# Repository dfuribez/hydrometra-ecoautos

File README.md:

View this project on [CADLAB.io](https://cadlab.io/project/2164).

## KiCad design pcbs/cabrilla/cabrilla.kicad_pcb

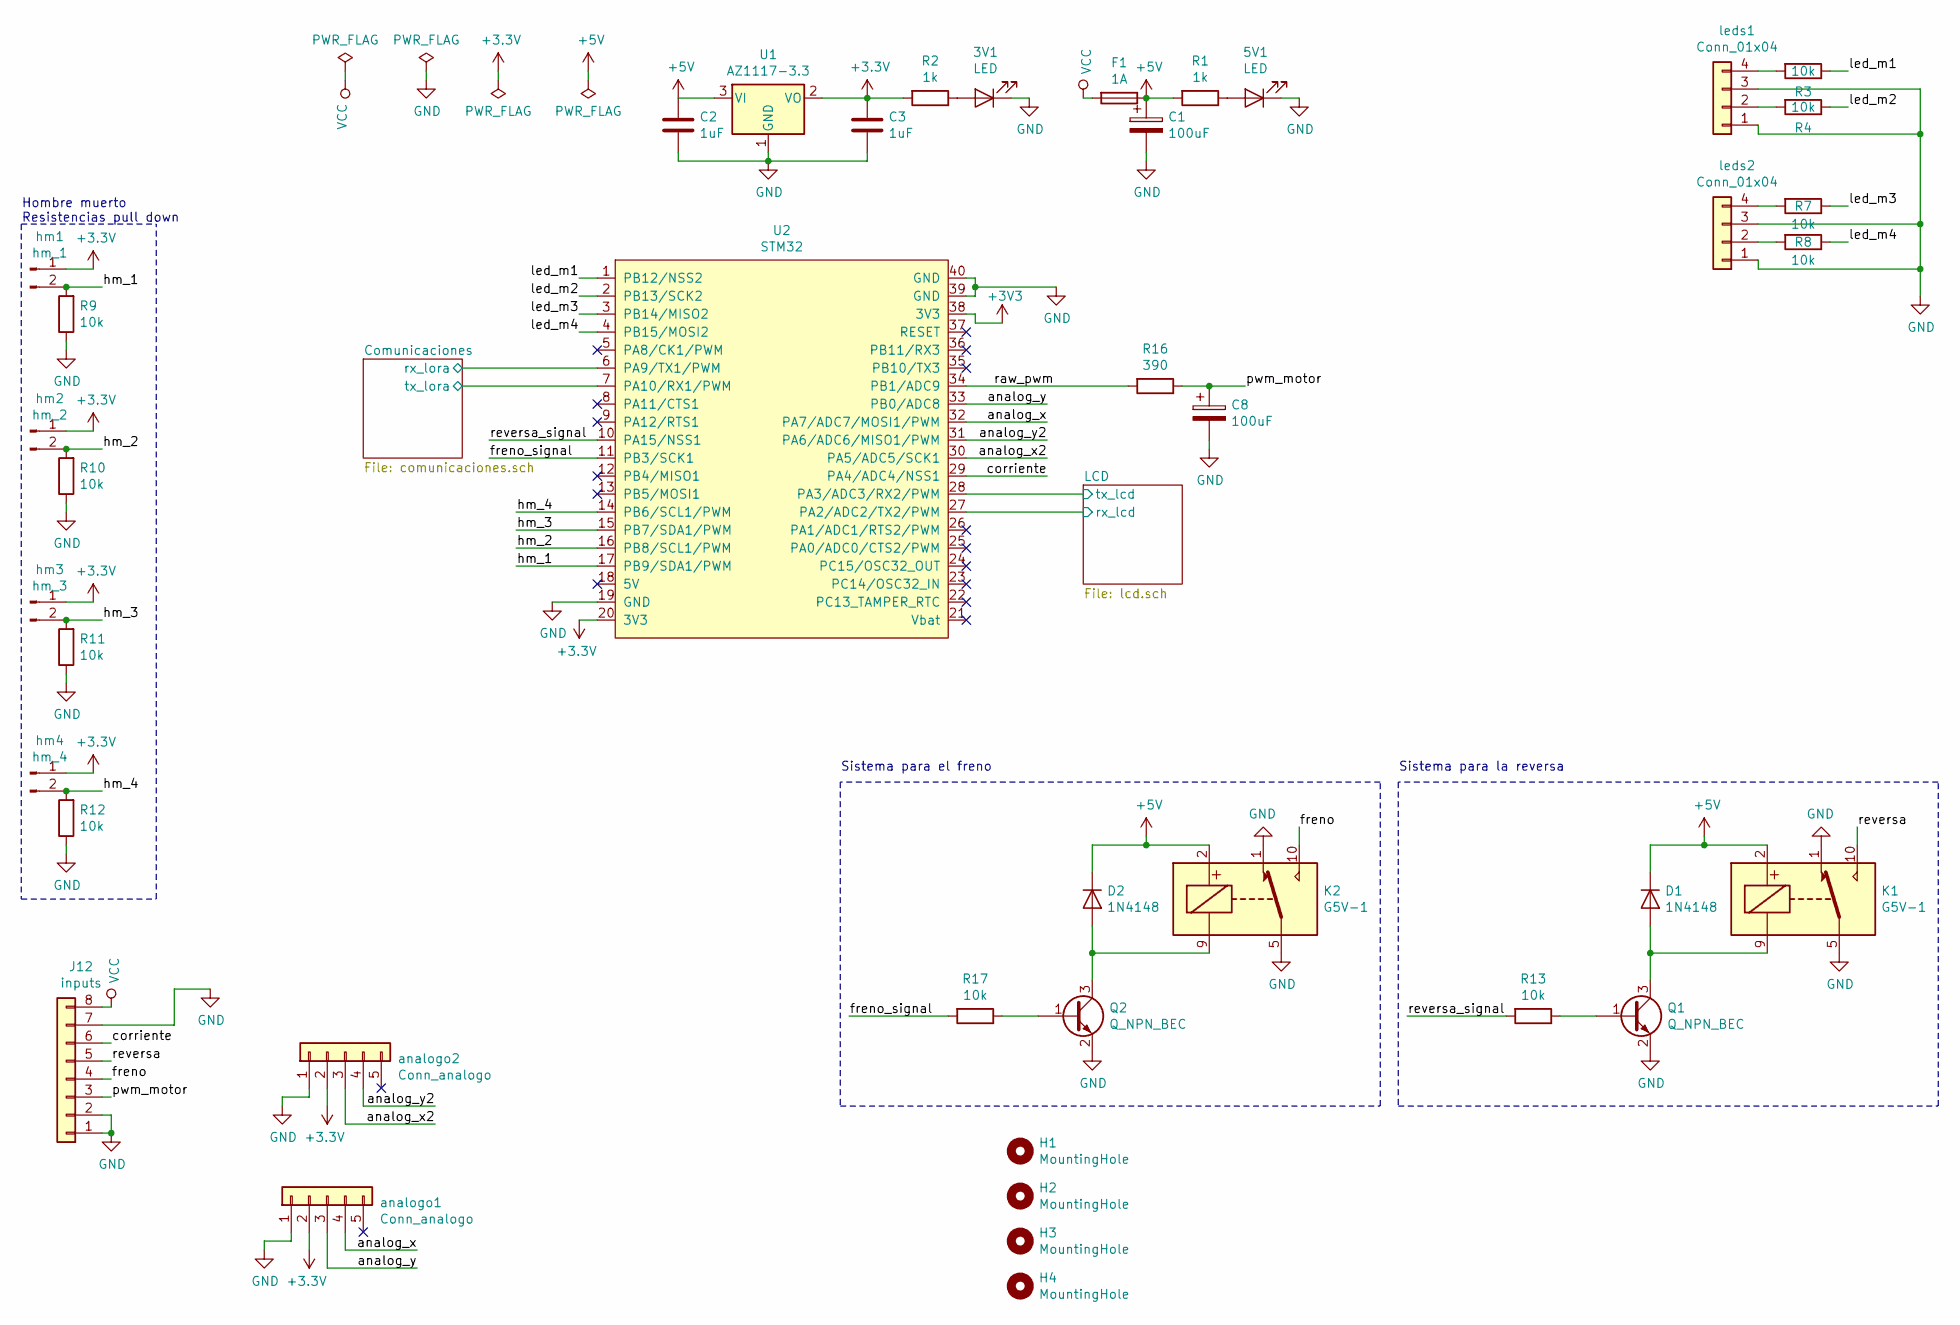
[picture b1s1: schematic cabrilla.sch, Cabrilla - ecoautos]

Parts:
3V1, 5V1: LED; LED_0805_2012Metric_Pad1.15x1.40mm_HandSolder
C1, C8: 100uF; CP_Elec_8x10
C2, C3: 1uF; C_0805_2012Metric_Pad1.15x1.40mm_HandSolder
D1, D2: 1N4148; D_SOD-323_HandSoldering
F1: 1A; Fuse_2816_7142Metric_Pad3.20x4.45mm_HandSolder
H1, H2, H3, H4: MountingHole; MountingHole_3.2mm_M3
J12: inputs; Molex_KK-254_AE-6410-08A_1x08_P2.54mm_Vertical
K1, K2: G5V-1; Relay_SPDT_Omron_G5V-1
Q1, Q2: Q_NPN_BEC; SOT-23_Handsoldering
R1, R2: 1k; R_0805_2012Metric_Pad1.15x1.40mm_HandSolder
R3, R4, R7, R8, R9, R10, R11, R12, R13, R17: 10k; R_0805_2012Metric_Pad1.15x1.40mm_HandSolder
R16: 390; R_0805_2012Metric_Pad1.15x1.40mm_HandSolder
U1: AZ1117-3.3; SOT-223
U2: STM32
analogo1, analogo2: Conn_analogo; Molex_KK-254_AE-6410-05A_1x05_P2.54mm_Vertical
hm1: hm_1; Molex_KK-254_AE-6410-02A_1x02_P2.54mm_Vertical
hm2: hm_2; Molex_KK-254_AE-6410-02A_1x02_P2.54mm_Vertical
hm3: hm_3; Molex_KK-254_AE-6410-02A_1x02_P2.54mm_Vertical
hm4: hm_4; Molex_KK-254_AE-6410-02A_1x02_P2.54mm_Vertical
leds1, leds2: Conn_01x04; Molex_KK-254_AE-6410-04A_1x04_P2.54mm_Vertical

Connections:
+5V: C1.1, C2.1, D1.1 (K), D2.1 (K), F1.1, K1.2, K2.2, R1.2, U1.3 (VI); also elsewhere on the board
/Comunicaciones/rx_lora: U2.6 (PA9/TX1/PWM); also elsewhere on the board
/Comunicaciones/tx_lora: U2.7 (PA10/RX1/PWM); also elsewhere on the board
/LCD/rx_lcd: U2.27 (PA2/ADC2/TX2/PWM); also elsewhere on the board
/LCD/tx_lcd: U2.28 (PA3/ADC3/RX2/PWM); also elsewhere on the board
/analog_x: U2.32 (PA7/ADC7/MOSI1/PWM), analogo1.4
/analog_x2: U2.30 (PA5/ADC5/SCK1), analogo2.3
/analog_y: U2.33 (PB0/ADC8), analogo1.3
/analog_y2: U2.31 (PA6/ADC6/MISO1/PWM), analogo2.4
/corriente: J12.6, U2.29 (PA4/ADC4/NSS1)
/freno: J12.4, K2.10
/freno_signal: R17.2, U2.11 (PB3/SCK1)
/hm_1: R9.2, U2.17 (PB9/SDA1/PWM), hm1.2
/hm_2: R10.2, U2.16 (PB8/SCL1/PWM), hm2.2
/hm_3: R11.2, U2.15 (PB7/SDA1/PWM), hm3.2
/hm_4: R12.2, U2.14 (PB6/SCL1/PWM), hm4.2
/led_m1: R3.1, U2.1 (PB12/NSS2)
/led_m2: R4.1, U2.2 (PB13/SCK2)
/led_m3: R7.1, U2.3 (PB14/MISO2)
/led_m4: R8.1, U2.4 (PB15/MOSI2)
/pwm_motor: C8.1, J12.3, R16.1
/raw_pwm: R16.2, U2.34 (PB1/ADC9)
/reversa: J12.5, K1.10
/reversa_signal: R13.2, U2.10 (PA15/NSS1)
GND: 3V1.1 (K), 5V1.1 (K), C1.2, C2.2, C3.2, C8.2, J12.1, J12.2, J12.7, K1.1, K1.5, K1.6, K2.1, K2.5, K2.6, Q1.2 (E), Q2.2 (E), R9.1, R10.1, R11.1, R12.1, U1.1 (GND), U2.19 (GND), U2.39 (GND), U2.40 (GND), analogo1.1, analogo2.1, leds1.1, leds1.3, leds2.1, leds2.3; also elsewhere on the board
unnamed: 3V1.2 (A), R2.1
unnamed: 5V1.2 (A), R1.1
unnamed: D1.2 (A), K1.9, Q1.3 (C)
unnamed: D2.2 (A), K2.9, Q2.3 (C)
unnamed: Q1.1 (B), R13.1
unnamed: Q2.1 (B), R17.1
unnamed: R3.2, leds1.4
unnamed: R4.2, leds1.2
unnamed: R7.2, leds2.4
unnamed: R8.2, leds2.2
VCC: F1.2, J12.8

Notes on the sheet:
Hombre muerto Resistencias pull down
Sistema para la reversa
Sistema para el freno

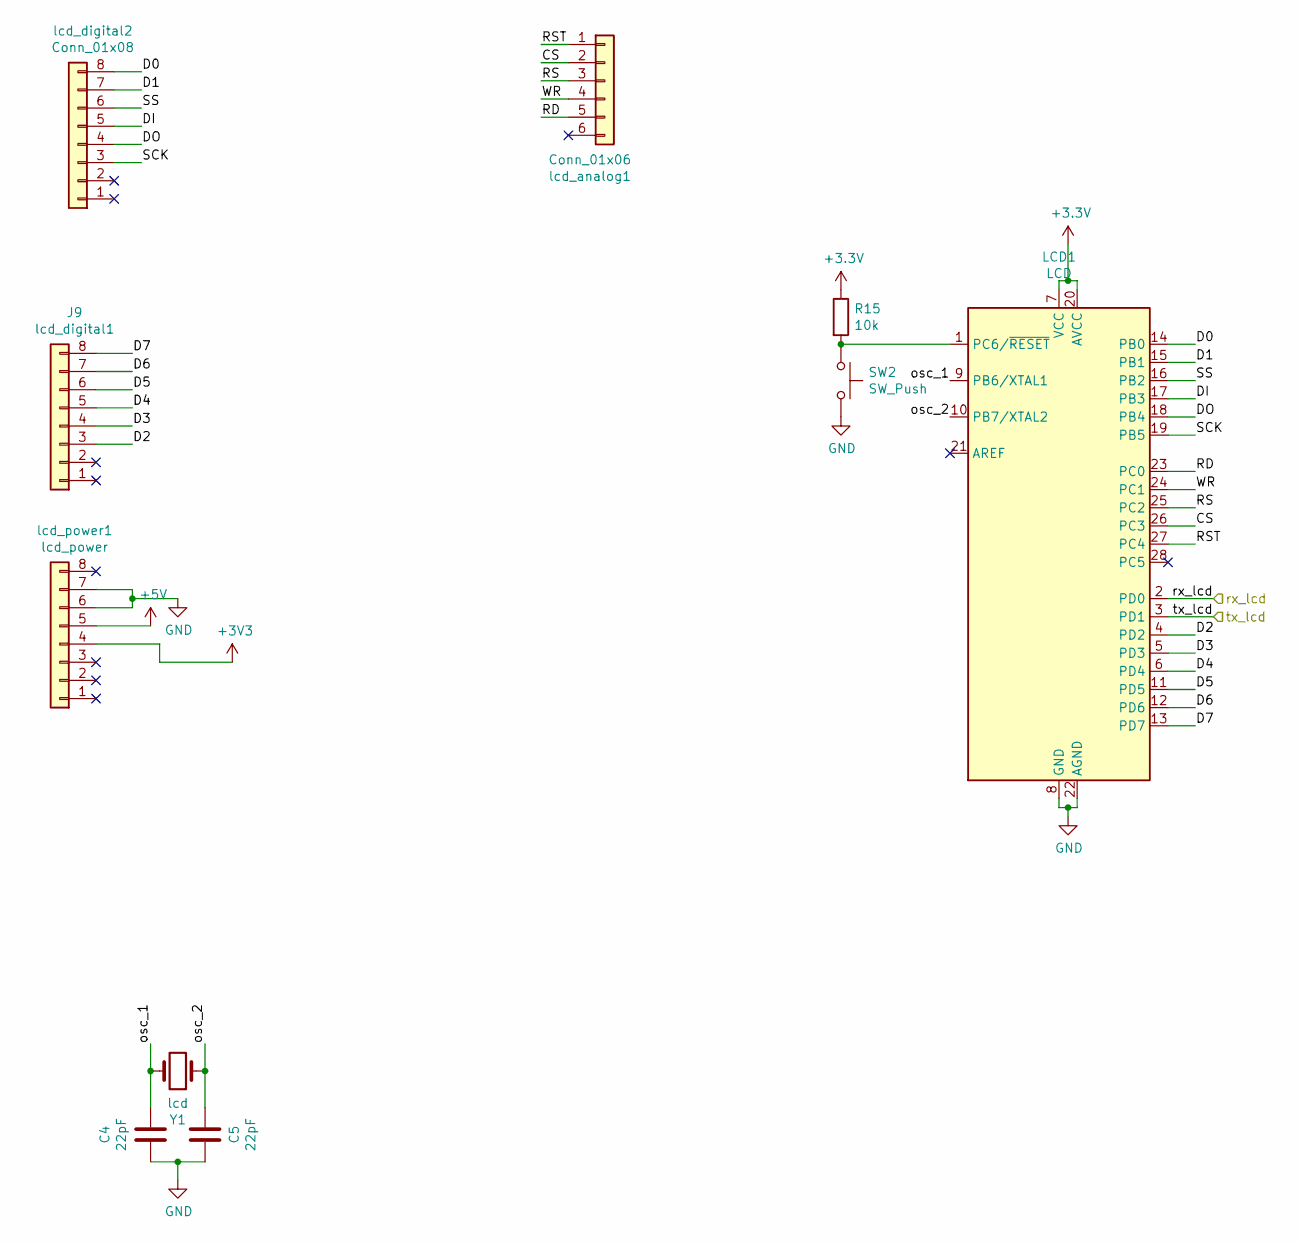
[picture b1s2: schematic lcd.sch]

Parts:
C4, C5: 22pF; C_0805_2012Metric_Pad1.15x1.40mm_HandSolder
J9: lcd_digital1; Molex_KK-254_AE-6410-08A_1x08_P2.54mm_Vertical
LCD1: LCD; DIP-28_W7.62mm_Socket
R15: 10k; R_0805_2012Metric_Pad1.15x1.40mm_HandSolder
SW2: SW_Push; SW_Push_1P1T_NO_CK_KSC6xxJ
Y1: lcd; Crystal_HC49-4H_Vertical
lcd_analog1: Conn_01x06; Molex_KK-254_AE-6410-06A_1x06_P2.54mm_Vertical
lcd_digital2: Conn_01x08; Molex_KK-254_AE-6410-08A_1x08_P2.54mm_Vertical
lcd_power1: lcd_power; Molex_KK-254_AE-6410-08A_1x08_P2.54mm_Vertical

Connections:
+5V: lcd_power1.5; also elsewhere on the board
/LCD/CS: LCD1.26 (PC3), lcd_analog1.2
/LCD/D0: LCD1.14 (PB0), lcd_digital2.8
/LCD/D1: LCD1.15 (PB1), lcd_digital2.7
/LCD/D2: J9.3, LCD1.4 (PD2)
/LCD/D3: J9.4, LCD1.5 (PD3)
/LCD/D4: J9.5, LCD1.6 (PD4)
/LCD/D5: J9.6, LCD1.11 (PD5)
/LCD/D6: J9.7, LCD1.12 (PD6)
/LCD/D7: J9.8, LCD1.13 (PD7)
/LCD/DI: LCD1.17 (PB3), lcd_digital2.5
/LCD/DO: LCD1.18 (PB4), lcd_digital2.4
/LCD/RD: LCD1.23 (PC0), lcd_analog1.5
/LCD/RS: LCD1.25 (PC2), lcd_analog1.3
/LCD/RST: LCD1.27 (PC4), lcd_analog1.1
/LCD/SCK: LCD1.19 (PB5), lcd_digital2.3
/LCD/SS: LCD1.16 (PB2), lcd_digital2.6
/LCD/WR: LCD1.24 (PC1), lcd_analog1.4
/LCD/osc_1: C4.2, LCD1.9 (PB6/XTAL1), Y1.2
/LCD/osc_2: C5.2, LCD1.10 (PB7/XTAL2), Y1.1
/LCD/rx_lcd: LCD1.2 (PD0); also elsewhere on the board
/LCD/tx_lcd: LCD1.3 (PD1); also elsewhere on the board
GND: C4.1, C5.1, LCD1.8 (GND), LCD1.22 (AGND), SW2.2, lcd_power1.6, lcd_power1.7; also elsewhere on the board
unnamed: LCD1.1 (PC6/~RESET), R15.2, SW2.1

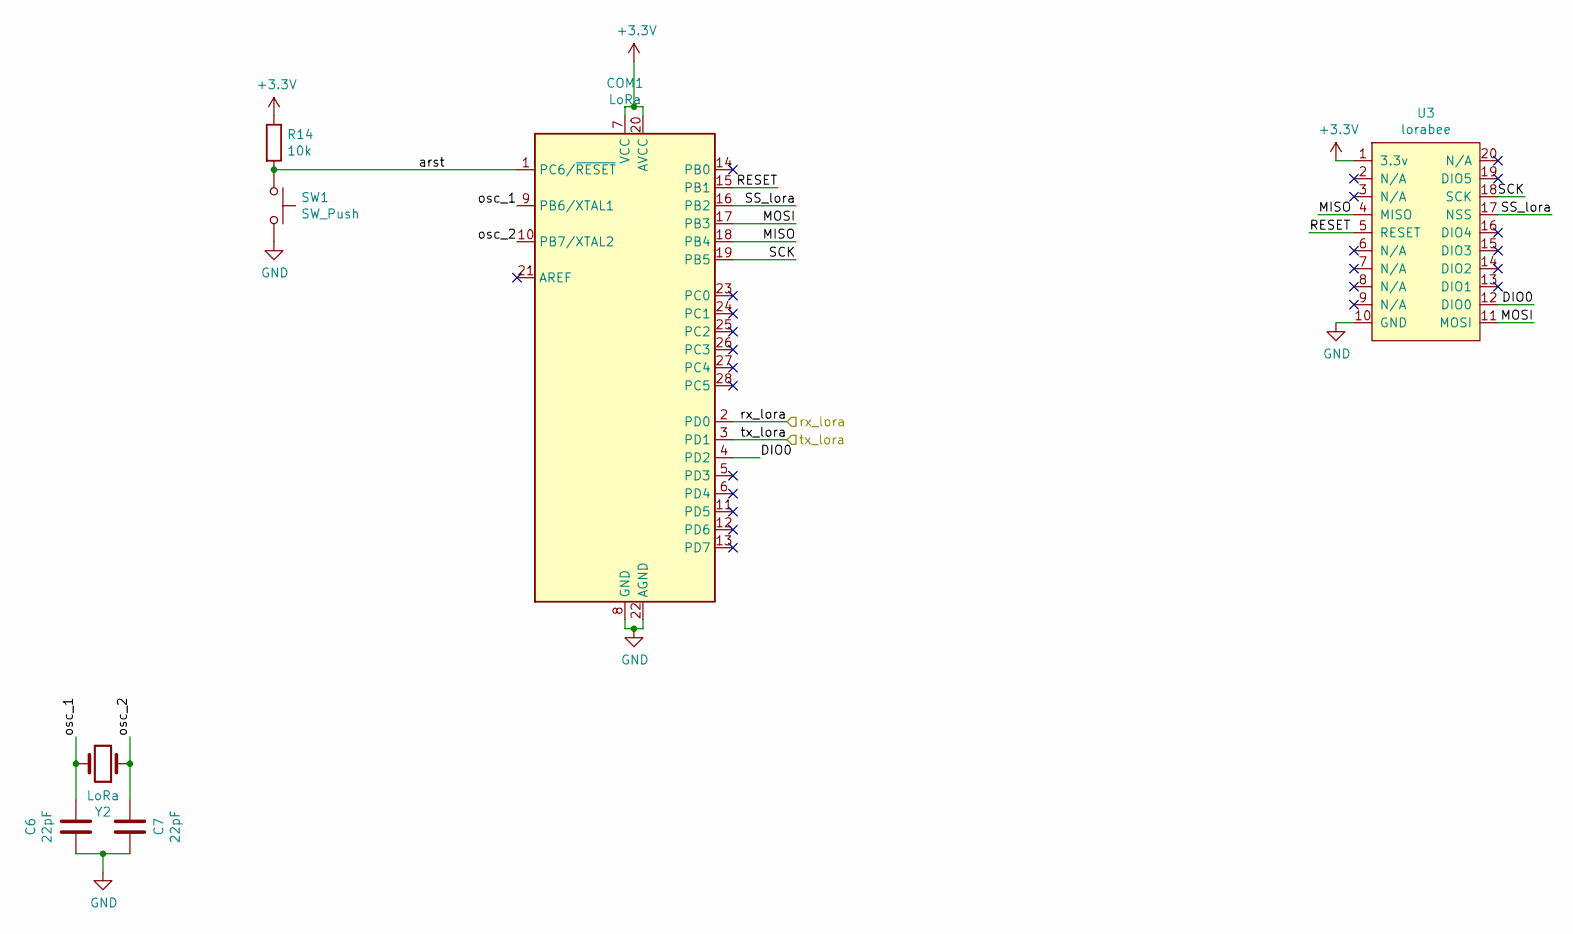
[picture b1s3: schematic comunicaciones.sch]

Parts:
C6, C7: 22pF; C_0805_2012Metric_Pad1.15x1.40mm_HandSolder
COM1: LoRa; DIP-28_W7.62mm_Socket
R14: 10k; R_0805_2012Metric_Pad1.15x1.40mm_HandSolder
SW1: SW_Push; SW_Push_1P1T_NO_CK_KSC6xxJ
U3: lorabee
Y2: LoRa; Crystal_HC49-4H_Vertical

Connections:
/Comunicaciones/DIO0: COM1.4 (PD2), U3.12 (DIO0)
/Comunicaciones/MISO: COM1.18 (PB4), U3.4 (MISO)
/Comunicaciones/MOSI: COM1.17 (PB3), U3.11 (MOSI)
/Comunicaciones/RESET: COM1.15 (PB1), U3.5 (RESET)
/Comunicaciones/SCK: COM1.19 (PB5), U3.18 (SCK)
/Comunicaciones/SS_lora: COM1.16 (PB2), U3.17 (NSS)
/Comunicaciones/arst: COM1.1 (PC6/~RESET), R14.2, SW1.1
/Comunicaciones/osc_1: C6.2, COM1.9 (PB6/XTAL1), Y2.2
/Comunicaciones/osc_2: C7.2, COM1.10 (PB7/XTAL2), Y2.1
/Comunicaciones/rx_lora: COM1.2 (PD0); also elsewhere on the board
/Comunicaciones/tx_lora: COM1.3 (PD1); also elsewhere on the board
GND: C6.1, C7.1, COM1.8 (GND), COM1.22 (AGND), SW1.2, U3.10 (GND); also elsewhere on the board

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
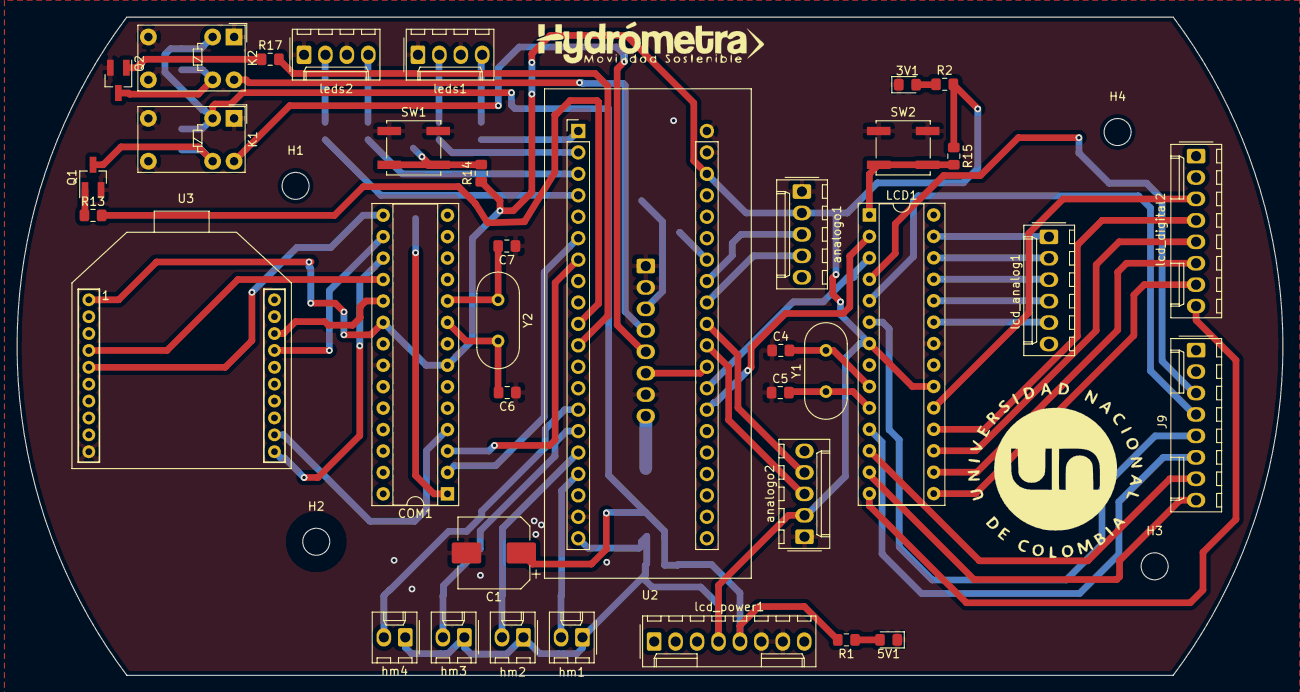
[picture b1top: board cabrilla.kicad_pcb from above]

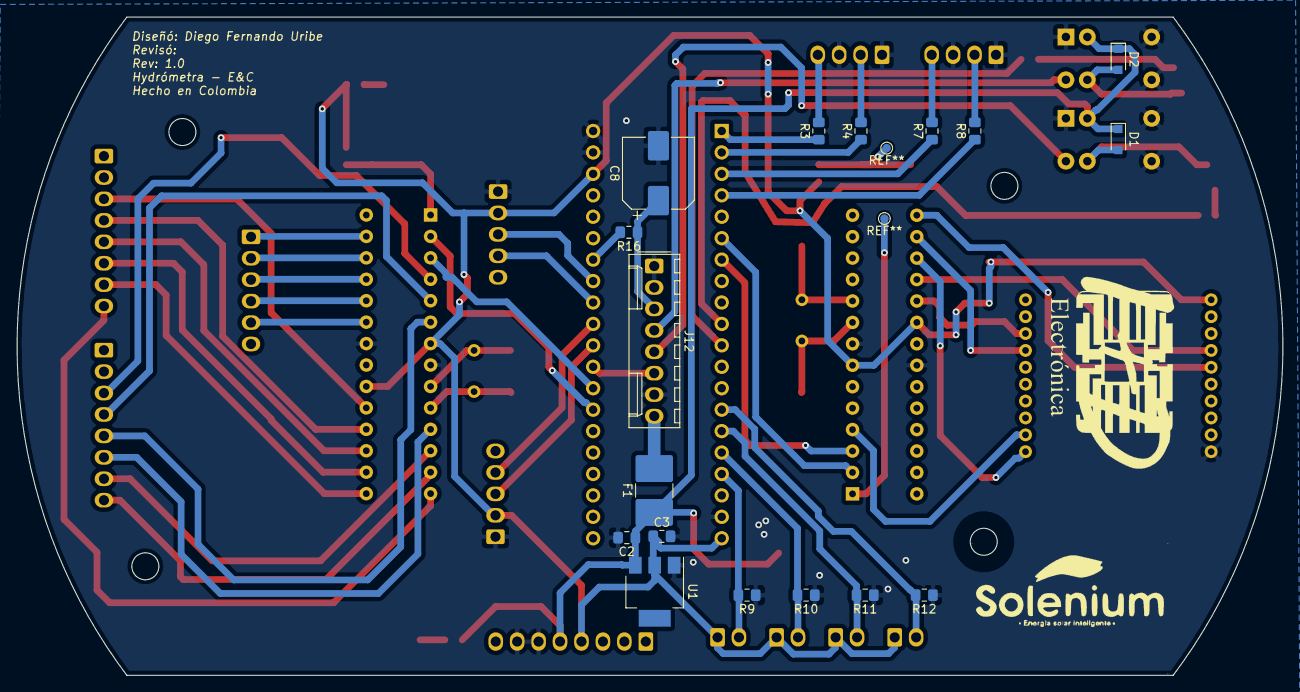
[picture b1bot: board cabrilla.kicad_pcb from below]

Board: 2 copper layers, 150.0 x 78.0 mm, 58 parts (17 on the bottom side), 66 nets.

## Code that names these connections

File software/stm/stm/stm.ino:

// Variables

// Análogo #1
uint16_t analog_x1 = 0;
uint16_t analog_y1 = 0;

// Análogo #2
uint16_t analog_x2 = 0;
uint16_t analog_y2 = 0;

uint8_t hm_counter = 0;


// Banderas interrupciones
bool flag_hm = 0;
bool flag_timer = 0;



// Pines

// Leds
#define LED_1_PIN   PB12
#define LED_2_PIN   PB13
#define LED_3_PIN   PB14
#define LED_4_PIN   PB15

#define REVERSA_PIN PA12
#define FRENO_PIN   PB3

// Hombre muerto
#define HM_1_PIN    PB6
#define HM_2_PIN    PB7
#define HM_3_PIN    PB8
#define HM_4_PIN    PB9

#define RAW_PWM_PIN     PB1

#define ANALOG_Y1_PIN   PB0
#define ANALOG_X1_PIN   PA7
#define ANALOG_Y2_PIN   PA6
#define ANALOG_X2_PIN   PA5

#define CORRIENTE_PIN   PA4


HardwareTimer timer(1);

// Definiciones
void isr_hm(void);  // Interrupción boton hombre muerto
void isr_timer(void);  // Interrupción timer hombre muerto

uint16_t read_analog(uint8_t pin);  // Lectura análoga
void generate_pwm(uint16_t valor); // Genera el pwm


void setup() {
  Serial.begin(115200);  // comunicaicones
  Serial1.begin(115200); // LCD

  pinMode(ANALOG_X1_PIN, INPUT_ANALOG);
  pinMode(ANALOG_Y1_PIN, INPUT_ANALOG);
  pinMode(ANALOG_X2_PIN, INPUT_ANALOG);
  pinMode(ANALOG_Y2_PIN, INPUT_ANALOG);
  pinMode(CORRIENTE_PIN, INPUT_ANALOG);

  pinMode(REVERSA_PIN, OUTPUT);
  pinMode(FRENO_PIN, OUTPUT);
  
  pinMode(LED_1_PIN, OUTPUT);
  pinMode(LED_2_PIN, OUTPUT);
  pinMode(LED_3_PIN, OUTPUT);
  pinMode(LED_4_PIN, OUTPUT);
  
  pinMode(HM_1_PIN, INPUT);
  pinMode(HM_2_PIN, INPUT);
  pinMode(HM_3_PIN, INPUT);
  pinMode(HM_4_PIN, INPUT);

  pinMode(RAW_PWM_PIN, PWM);


  // Interrupciones
  attachInterrupt(digitalPinToInterrupt(HM_1_PIN), isr_hm, CHANGE);
  attachInterrupt(digitalPinToInterrupt(HM_2_PIN), isr_hm, CHANGE);
  attachInterrupt(digitalPinToInterrupt(HM_3_PIN), isr_hm, CHANGE);
  attachInterrupt(digitalPinToInterrupt(HM_4_PIN), isr_hm, CHANGE);


  // Timer
  timer.pause();  // Pausa el timer
  timer.setMode(TIMER_CH1, TIMER_OUTPUT_COMPARE);
  timer.setPeriod(1000000);
  timer.attachCompare1Interrupt(isr_timer);  // Interrupción
  timer.refresh();  // Resetea el timer
  timer.resume();  // Inicia el timer
}


void loop() {
  

}


void isr_hm() {
  /*
  Función que se llama al ocurrir una interrupción
  en los botones del sistema de hombre muerto.
  */
  
}


void isr_timer() {
  /*
   * función que es llamada cuando se desborda el timer
   * que cuenta el tiempo de hombre muerto
  */
}


uint16_t read_analog(uint8_t pin) {
  /*
   * Funciónq ue se encarga de hacer la correcta lectura de
   * los sensores anñálogos. Lo hace mediante dos mediciones
   * para darle tiempo al ADC de cargarse y leer adecuadamente
   * 
   * @pin pin a ser leido
   * Devuelve el valor del ADC 12bits
  */
  
  analogRead(pin);  // Desecha la primer medida
  delay(10);  // Espera
  return analogRead(pin);  // Devuelve la medida correcta
}

void generate_pwm(uint16_t valor) {
  /*
   * Función que genera el pwm según el valor ADC leído
   * 
   * @valor valor análogo para calcular el PWM
   * Devuelve un PWM de 16bits
  */

  uint16_t pwm_value;
  uint32_t contador;

  if (valor > 2090) {
    pwm_value = map(valor, 2090, 4095, 19000, 65535);

    if (pwm_value > 65535) pwm_value = 65535;

    digitalWrite(REVERSA_PIN, LOW);

    if (pwm_value > 29789) { // 29789 -> 1.5V
      contador = 19000;
      while (contador <= pwm_value) {
        pwmWrite(RAW_PWM_PIN, contador);
        delay(100);
        contador += 20000; // 2000 equivale a incremento de 1V
      } // end while
    } else {  //end if-pwm_value
      pwmWrite(RAW_PWM_PIN, pwm_value);
    }  // end else

  } else if(valor < 2050)  {// reversa
    pwm_value = map(valor, 0, 2050, 65535, 19000);

    if (pwm_value > 65535) pwm_value = 65535;

    digitalWrite(REVERSA_PIN, HIGH);
    pwmWrite(RAW_PWM_PIN, pwm_value);
    
  } // end if-valor
} //end generate_pwm

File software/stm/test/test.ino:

bool flag_hm = 0;
bool flag_timer = 0;
uint16_t x = 0;
uint16_t y = 0;

uint16_t x_prev = 0;
uint16_t y_prev = 0;


uint16_t y_prob = 0;
uint8_t time_counter = 0;

uint32_t j = 0;



#define reversa         PB5 // Pin para la reversa
#define analogo_x       PA7 // Eje del análogo - ADC
#define analogo_y       PA6 // Otro eje del análogo - ADC
#define pwm_motor       PB1 // Pin PWM del motor - PWM
#define hm_1            PA5
#define hm_2            PA4
#define hm_3            PA1
#define hm_4            PA0

#define test            PB3
#define led             PC13


#define dead_man_seconds    3

HardwareTimer timer(1);

void setup() {
  Serial.begin(115200);  // Debug
  Serial1.begin(115200);  // Comunicaciones
  Serial2.begin(115200);  // LCD
  
  // Conversiones análogas
  pinMode(analogo_x, INPUT_ANALOG);
  pinMode(analogo_y, INPUT_ANALOG);

  // Salidas
  pinMode(reversa, OUTPUT);
  pinMode(test, OUTPUT);
  pinMode(led, OUTPUT);

  // PWMs
  pinMode(pwm_motor, PWM);
  pwmWrite(pwm_motor, 0);

  // Entradas
  pinMode(hm_1, INPUT);
  pinMode(hm_2, INPUT);
  pinMode(hm_3, INPUT);
  pinMode(hm_4, INPUT);


  // Interrupciones
  /*
  attachInterrupt(digitalPinToInterrupt(hm_1), int_hm, CHANGE);
  attachInterrupt(digitalPinToInterrupt(hm_2), int_hm, CHANGE);
  attachInterrupt(digitalPinToInterrupt(hm_3), int_hm, CHANGE);
  attachInterrupt(digitalPinToInterrupt(hm_4), int_hm, CHANGE);
  */

  // Timer
  
  timer.pause();
  timer.setMode(TIMER_CH1, TIMER_OUTPUT_COMPARE);
  timer.setPeriod(1000000);
  timer.attachCompare1Interrupt(reloj);
  timer.refresh();  // Resetea el timer
  //timer.resume();  // Inicia el timer
  
  Serial.println("Iniciabndo");
  digitalWrite(led, HIGH);
  digitalWrite(test, HIGH);
  digitalWrite(reversa, HIGH);
}

void loop() {
  // put your main code here, to run repeatedly:
  analogRead(analogo_x);
  delay(10);
  x = analogRead(analogo_x);
  delay(100);
  analogRead(analogo_y);
  delay(10);
  
  y = analogRead(analogo_y);

  if (y > 2090) {

    y_prev = y_prob;
    y_prob = map(y, 2090, 4095, 19000, 65535);

    if (y_prob > 65535) {
      y_prob = 65535;
    }

    digitalWrite(reversa, HIGH);
    Serial.print("adelante, ");
    Serial.print(y);
    Serial.print(", ");
    Serial.println(y_prob);


    if (y_prev < y_prob - 2000) {
      // lanza la curva
      if (y_prob > 29789) {  // 29789 -> 1.5V
        //for (uint16_t j=19000; j<=y_prob; j=j+2000) {
        j = 19000;
        while (j < y_prob) {
          pwmWrite(pwm_motor, j);
          Serial.println(j);
          delay(100);
          j = j + 2000;
        }
      }
    }
    
    
    pwmWrite(pwm_motor, y_prob);

  } else if (y < 2050) {
    y_prob = map(y, 0, 2050, 65535, 19000);

    if (y_prob > 65535) {
      y_prob = 65535;
    }
    
    pwmWrite(pwm_motor, y_prob);
    digitalWrite(reversa, LOW);
    Serial.print("Reversa, "); 
    Serial.print(y);
    Serial.print(", ");
    Serial.println(y_prob);
  } else {
    pwmWrite(pwm_motor, 0);
  }
  
  if (flag_hm) {
    Serial.println("Hombre Muerto");
    flag_hm = 0;
  } // end-if flag hombre muerto
 
  if (flag_timer) {
    //Serial.println("timerrrrr");
    digitalWrite(test, !digitalRead(test));
    digitalWrite(led, !digitalRead(led));

    
    timer.refresh();
    flag_timer = 0;
    timer.resume();
    
  } // end-if flag timer

  if (time_counter >= dead_man_seconds) {
    
  }
  
}

/* rutinas interrupciones */

void int_hm() {
  /* Sistema de hombre muerto */
  if (digitalRead(hm_1) || digitalRead(hm_2) || digitalRead(hm_3) || digitalRead(hm_4)) {
    // nothing
  } else {
    flag_hm = 1;
  }
}

void reloj() {
  timer.pause();
  timer.refresh();
  flag_timer = 1;
}

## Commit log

2019-09-25 Initial structure
2019-09-25 Initial design
2019-09-25 Added Hydrómetra logo
2019-09-25 Added symbol for the STM32 microcontroller.
2019-09-25 Deleted temporary files
2019-09-26 functionality test
2019-09-27 STM32 footprint
2019-09-27 Changed hm_3 and hm_4 pins
2019-09-27 Discards first analog measurement.
2019-09-27 Added STM32
2019-09-28 Backlink to CADLAB.io has been added.
2019-09-28 cache libraries
2019-09-30 Changed timer3 for timer1 and fixed PWM problem.
2019-10-01 ixed
2019-10-02 Fixed PWM
2019-10-07 Updated footprints
2019-10-08 Routed
2019-10-08 Add soft start
2019-10-08 Final
2019-10-10 Cambiados los parámetros de rutero
2019-10-10 Programa final
2019-10-11 GUI inicial para pits
2019-10-11 Agregado hilos para la actualización de la GUI
2019-10-11 Agregado conteo de vueltas
2019-10-11 Agregada función para almacenar los datos leídos
